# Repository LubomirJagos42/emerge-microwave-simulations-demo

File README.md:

# emerge-microwave-simulations-demo
FEM simulations examples python scripts for EMerge.

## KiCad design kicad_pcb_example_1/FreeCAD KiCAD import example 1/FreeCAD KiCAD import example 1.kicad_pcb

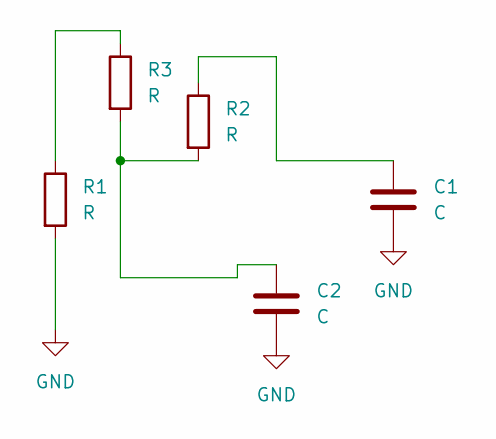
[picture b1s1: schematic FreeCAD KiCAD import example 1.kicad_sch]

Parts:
C1, C2: C; C_1206_3216Metric
R1, R2, R3: R; R_1206_3216Metric

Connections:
GND: C1.2, C2.2, R1.2
unnamed: C1.1, R2.1
unnamed: C2.1, R2.2, R3.2
unnamed: R1.1, R3.1

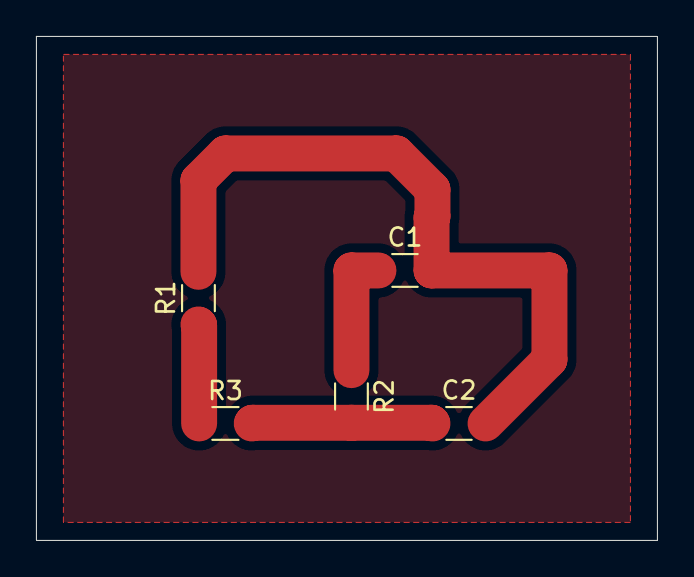
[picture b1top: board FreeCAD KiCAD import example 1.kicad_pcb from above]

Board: 2 copper layers, 34.5 x 28.0 mm, 5 parts (0 on the bottom side), 4 nets.

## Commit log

2026-04-01 added all results as I forgot to add them for loooong time
2026-04-01 added all local examples to git
